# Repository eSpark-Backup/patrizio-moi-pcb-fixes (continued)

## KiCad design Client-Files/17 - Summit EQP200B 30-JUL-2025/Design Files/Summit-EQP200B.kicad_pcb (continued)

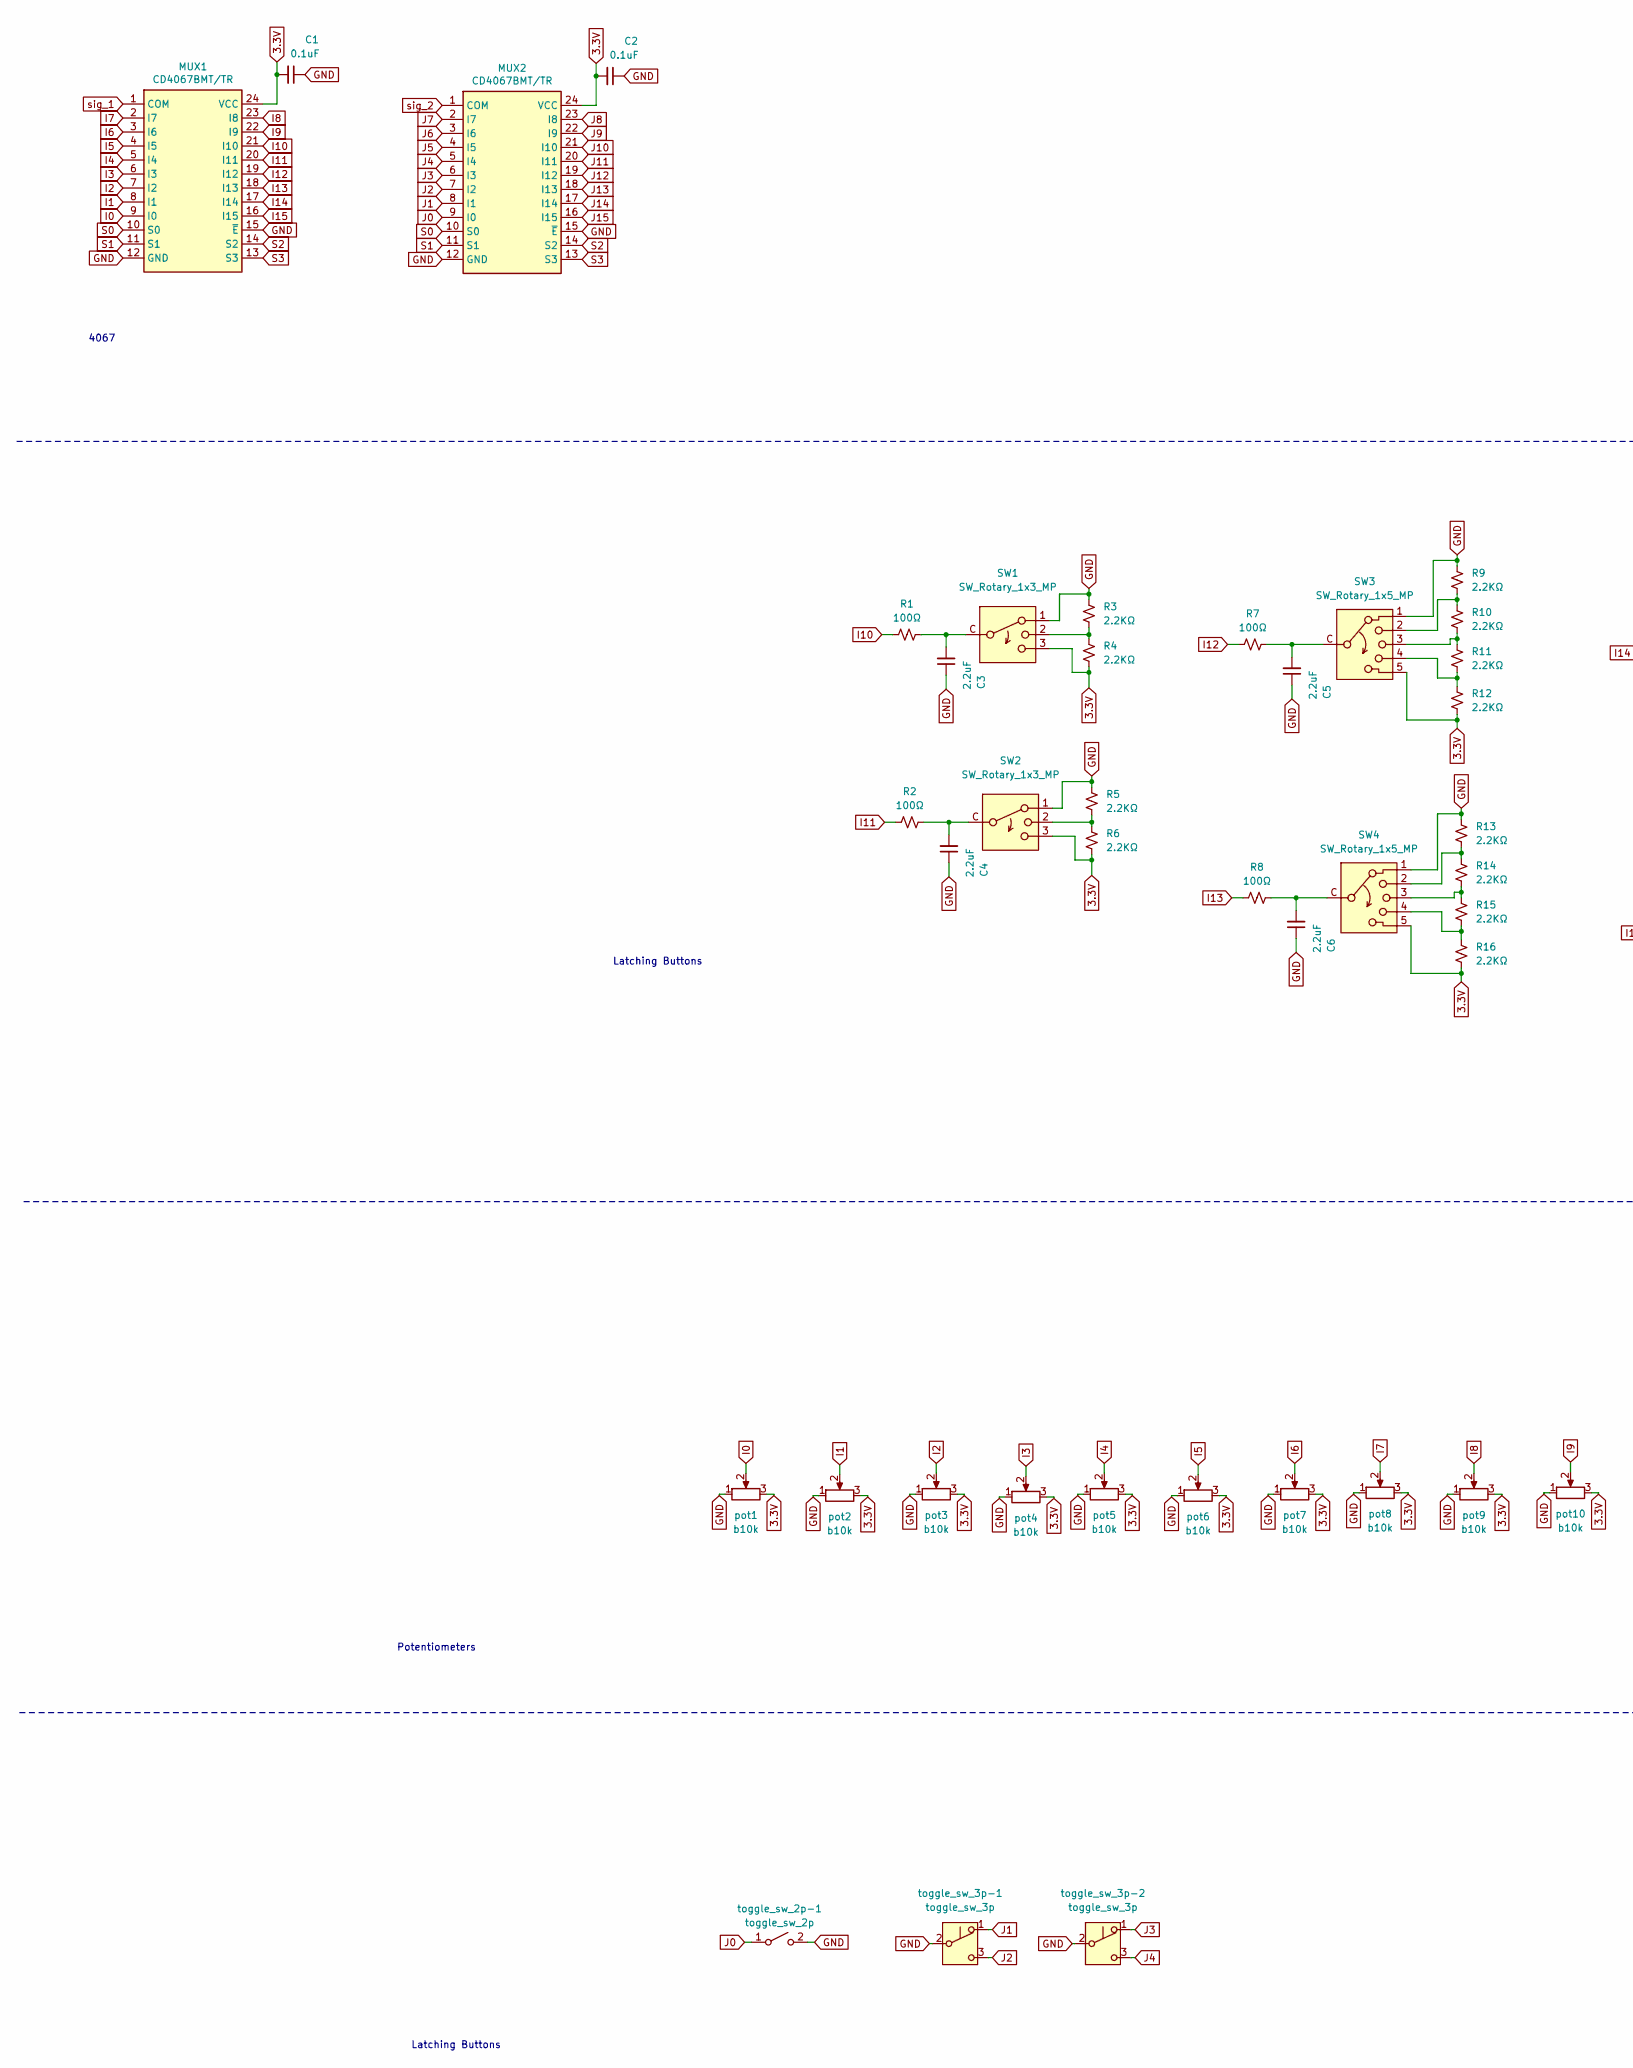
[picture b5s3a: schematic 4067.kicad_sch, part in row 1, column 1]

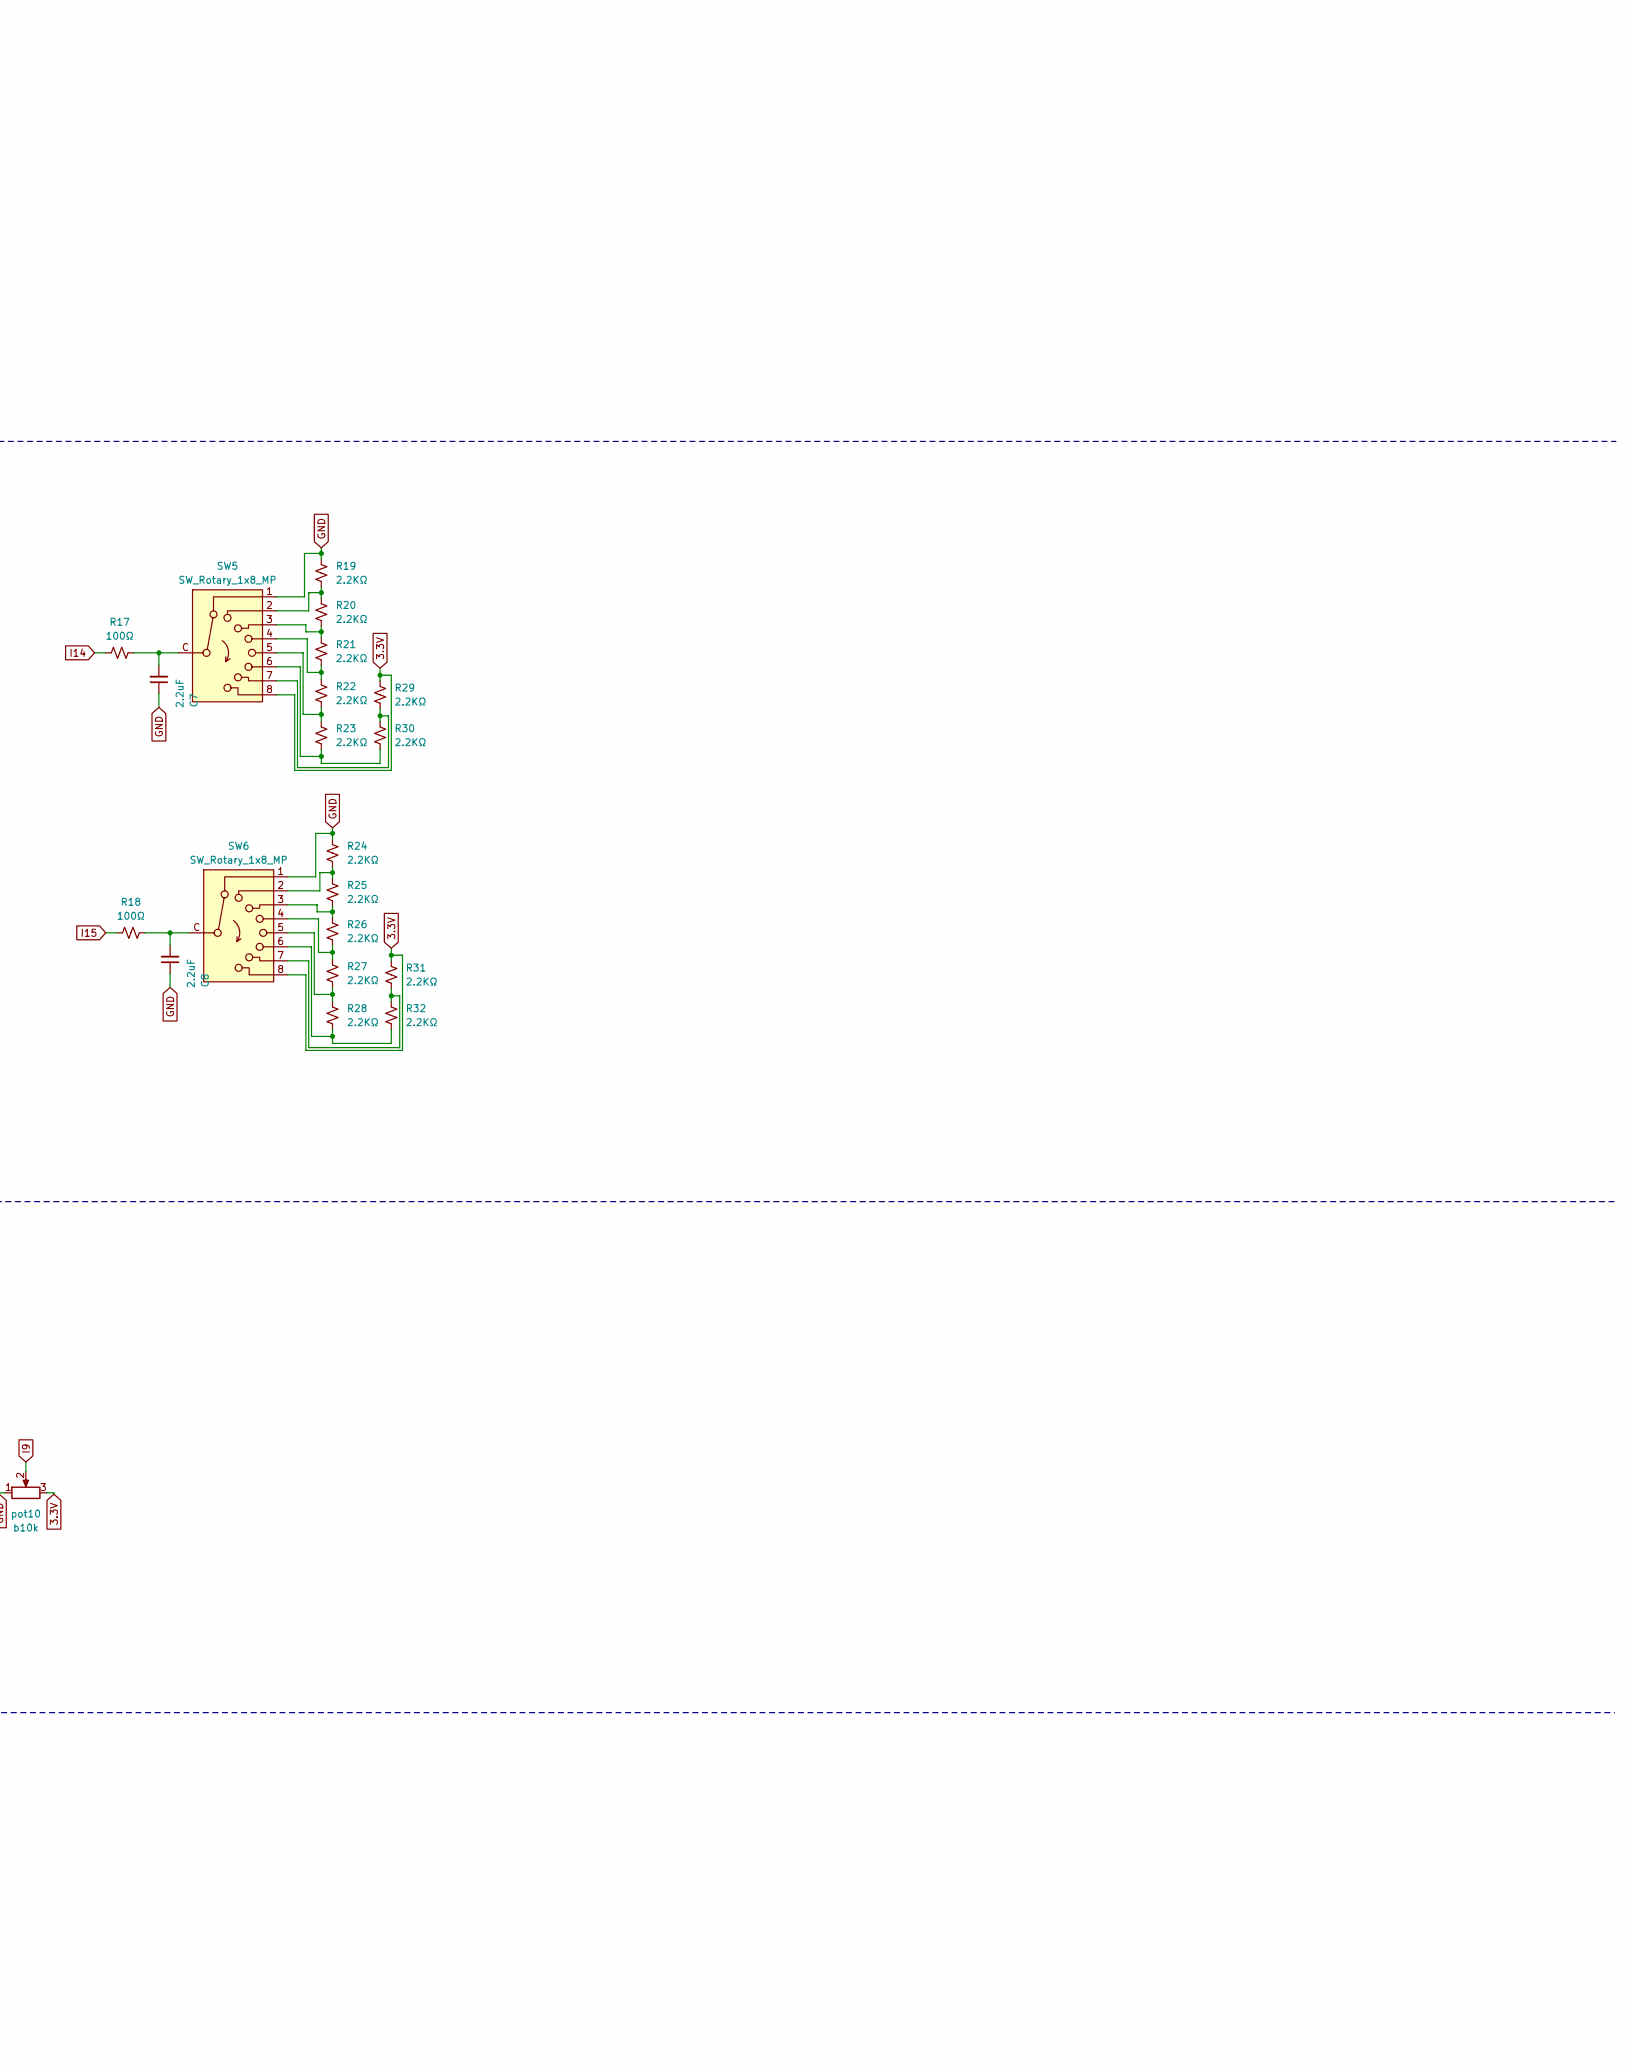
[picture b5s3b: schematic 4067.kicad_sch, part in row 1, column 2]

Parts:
C1, C2: 0.1uF; C_0402_1005Metric; LCSC Part Number C1525
C3, C4, C5, C6, C7, C8: 2.2uF; C_0402_1005Metric; LCSC Part Number C12530
MUX1, MUX2: CD4067BMT/TR; TSSOP-24_4.4x7.8mm_P0.65mm; LCSC Part Number C7432333
R1, R2, R7, R8, R17, R18: 100Ω; R_0402_1005Metric; LCSC Part Number C25076
R3, R4, R5, R6, R9, R10, R11, R12, R13, R14, R15, R16, R19, R20, R21, R22, R23, R24, R25, R26, R27, R28, R29, R30, R31, R32: 2.2KΩ; R_0402_1005Metric; LCSC Part Number C25879
SW1, SW2: SW_Rotary_1x3_MP; SW_Rotary_RS25-3P
SW3, SW4: SW_Rotary_1x5_MP; SW_Rotary_RS25-5P
SW5, SW6: SW_Rotary_1x8_MP; SW_Rotary_RS25-8P
pot1, pot2, pot3, pot4, pot5, pot6, pot7, pot8, pot9, pot10: b10k; Potentiometer_Alps_RK09K_Single_Vertical
toggle_sw_2p-1: toggle_sw_2p; Toggle_Switch-2-pins
toggle_sw_3p-1, toggle_sw_3p-2: toggle_sw_3p; Toggle_Switch-3-pins

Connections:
3.3V: C1.2, C2.2, MUX1.24 (VCC), MUX2.24 (VCC), R4.1, R6.1, R12.1, R16.1, R29.2, R31.2, SW1.3, SW2.3, SW3.5, SW4.5, SW5.8, SW6.8, pot1.3, pot2.3, pot3.3, pot4.3, pot5.3, pot6.3, pot7.3, pot8.3, pot9.3, pot10.3; also elsewhere on the board
GND: C1.1, C2.1, C3.1, C4.1, C5.1, C6.1, C7.1, C8.1, MUX1.12 (GND), MUX1.15 (~E), MUX2.12 (GND), MUX2.15 (~E), R3.2, R5.2, R9.2, R13.2, R19.2, R24.2, SW1.1, SW2.1, SW3.1, SW4.1, SW5.1, SW6.1, pot1.1, pot2.1, pot3.1, pot4.1, pot5.1, pot6.1, pot7.1, pot8.1, pot9.1, pot10.1, toggle_sw_2p-1.2 (B), toggle_sw_3p-1.2 (B), toggle_sw_3p-2.2 (B); also elsewhere on the board
I0: MUX1.9 (I0), pot1.2
I1: MUX1.8 (I1), pot2.2
I2: MUX1.7 (I2), pot3.2
I3: MUX1.6 (I3), pot4.2
I4: MUX1.5 (I4), pot5.2
I5: MUX1.4 (I5), pot6.2
I6: MUX1.3 (I6), pot7.2
I7: MUX1.2 (I7), pot8.2
I8: MUX1.23 (I8), pot9.2
I9: MUX1.22 (I9), pot10.2
I10: MUX1.21 (I10), R1.1
I11: MUX1.20 (I11), R2.1
I12: MUX1.19 (I12), R7.1
I13: MUX1.18 (I13), R8.1
I14: MUX1.17 (I14), R17.1
I15: MUX1.16 (I15), R18.1
J0: MUX2.9 (I0), toggle_sw_2p-1.1 (A)
J1: MUX2.8 (I1), toggle_sw_3p-1.1 (A)
J2: MUX2.7 (I2), toggle_sw_3p-1.3 (C)
J3: MUX2.6 (I3), toggle_sw_3p-2.1 (A)
J4: MUX2.5 (I4), toggle_sw_3p-2.3 (C)
J5: MUX2.4 (I5)
J6: MUX2.3 (I6)
J7: MUX2.2 (I7)
J8: MUX2.23 (I8)
J9: MUX2.22 (I9)
J10: MUX2.21 (I10)
J11: MUX2.20 (I11)
J12: MUX2.19 (I12)
J13: MUX2.18 (I13)
J14: MUX2.17 (I14)
J15: MUX2.16 (I15)
unnamed: C3.2, R1.2, SW1.C
unnamed: C4.2, R2.2, SW2.C
unnamed: C5.2, R7.2, SW3.C
unnamed: C6.2, R8.2, SW4.C
unnamed: C7.2, R17.2, SW5.C
unnamed: C8.2, R18.2, SW6.C
unnamed: R3.1, R4.2, SW1.2
unnamed: R5.1, R6.2, SW2.2
unnamed: R10.1, R11.2, SW3.3
unnamed: R9.1, R10.2, SW3.2
unnamed: R11.1, R12.2, SW3.4
unnamed: R13.1, R14.2, SW4.2
unnamed: R14.1, R15.2, SW4.3
unnamed: R15.1, R16.2, SW4.4
unnamed: R19.1, R20.2, SW5.2
unnamed: R20.1, R21.2, SW5.3
unnamed: R21.1, R22.2, SW5.4
unnamed: R22.1, R23.2, SW5.5
unnamed: R23.1, R30.1, SW5.6
unnamed: R24.1, R25.2, SW6.2
unnamed: R25.1, R26.2, SW6.3
unnamed: R26.1, R27.2, SW6.4
unnamed: R27.1, R28.2, SW6.5
unnamed: R28.1, R32.1, SW6.6
unnamed: R29.1, R30.2, SW5.7
unnamed: R31.1, R32.2, SW6.7
S0: MUX1.10 (S0), MUX2.10 (S0); also elsewhere on the board
S1: MUX1.11 (S1), MUX2.11 (S1); also elsewhere on the board
S2: MUX1.14 (S2), MUX2.14 (S2); also elsewhere on the board
S3: MUX1.13 (S3), MUX2.13 (S3); also elsewhere on the board
sig_1: MUX1.1 (COM); also elsewhere on the board
sig_2: MUX2.1 (COM); also elsewhere on the board

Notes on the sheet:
Latching Buttons
Potentiometers
4067

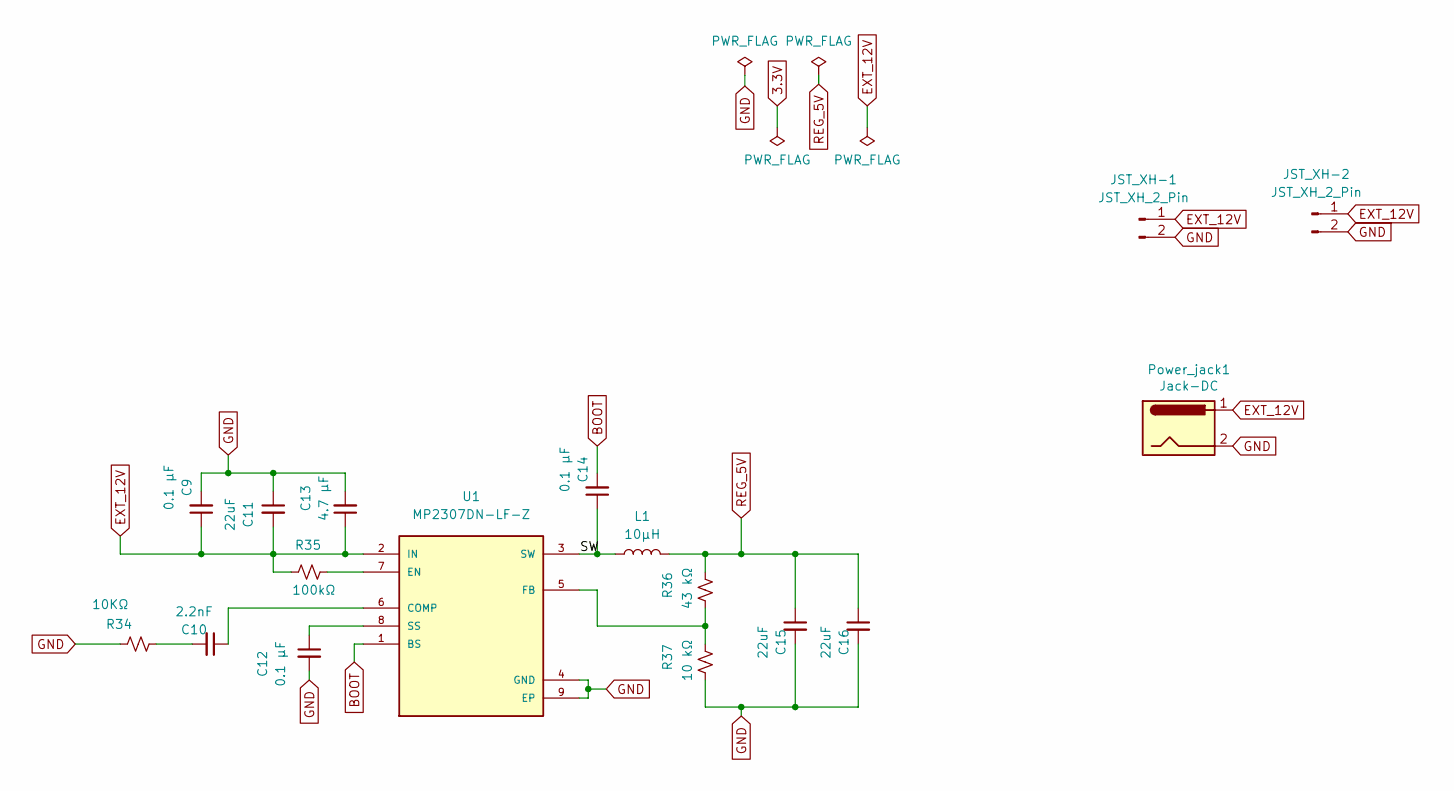
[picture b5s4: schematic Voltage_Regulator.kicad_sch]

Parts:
C9, C12, C14: 0.1 µF; C_0402_1005Metric; LCSC Part Number C1525
C10: 2.2nF; C_0603_1608Metric; LCSC Part Number C1604
C11, C15, C16: 22uF; C_0603_1608Metric; LCSC Part Number C59461
C13: 4.7 µF; C_0402_1005Metric; LCSC Part Number C23733
JST_XH-1, JST_XH-2: JST_XH_2_Pin; JST_XH_B2B-XH-A_1x02_P2.50mm_Vertical
L1: 10µH; L_Bourns-SRN8040_8x8.15mm; LCSC Part Number C37429
Power_jack1: Jack-DC; BarrelJack_Horizontal
R34: 10KΩ; R_0603_1608Metric; LCSC Part Number C25744
R35: 100kΩ; R_0603_1608Metric; LCSC Part Number C23212
R36: 43 kΩ; R_0402_1005Metric; LCSC Part Number C2906943
R37: 10 kΩ; R_0402_1005Metric; LCSC Part Number C25744
U1: MP2307DN-LF-Z; SOIC-8-1EP_3.9x4.9mm_P1.27mm_EP2.29x3mm_ThermalVias; PARTREV 1.9; LCSC Part Number C2928813

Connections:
/Voltage_Regulator/SW: C14.1, L1.1, U1.3 (SW)
BOOT: C14.2, U1.1 (BS)
EXT_12V: C9.1, C11.2, C13.1, JST_XH-1.1, JST_XH-2.1, Power_jack1.1, R35.1, U1.2 (IN)
GND: C9.2, C11.1, C12.2, C13.2, C15.2, C16.2, JST_XH-1.2, JST_XH-2.2, Power_jack1.2, R34.1, R37.2, U1.4 (GND), U1.9 (EP); also elsewhere on the board
unnamed: C10.2, R34.2
unnamed: C10.1, U1.6 (COMP)
unnamed: R35.2, U1.7 (EN)
unnamed: R36.2, R37.1, U1.5 (FB)
unnamed: C12.1, U1.8 (SS)
REG_5V: C15.1, C16.1, L1.2, R36.1; also elsewhere on the board

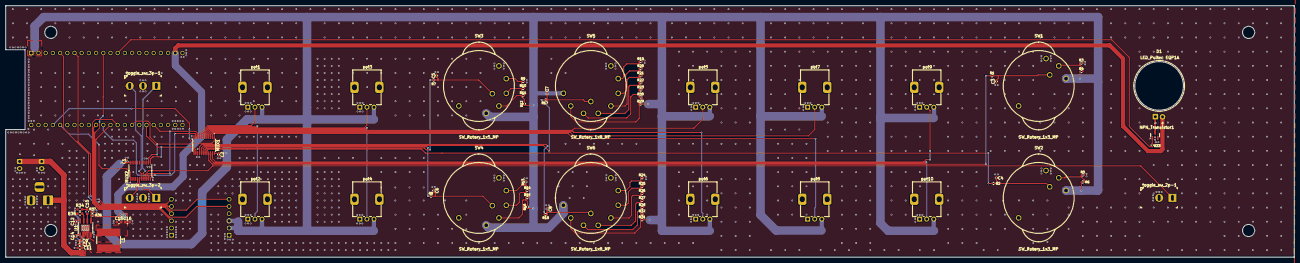
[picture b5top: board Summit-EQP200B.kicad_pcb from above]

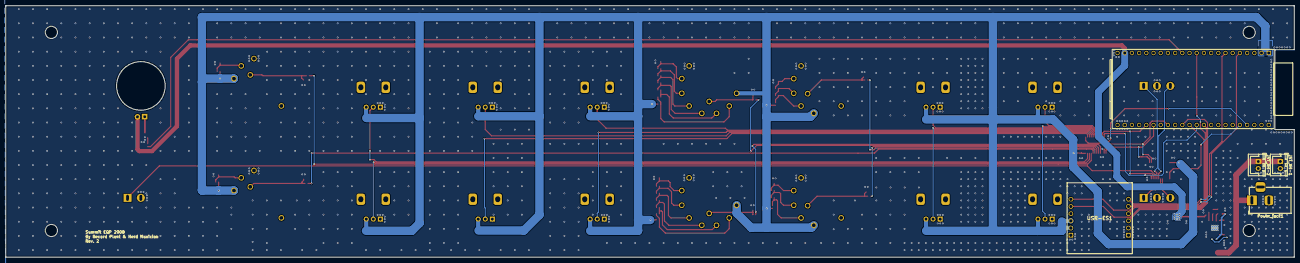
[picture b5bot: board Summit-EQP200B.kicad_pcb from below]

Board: 2 copper layers, 454.6 x 88.7 mm, 83 parts (5 on the bottom side), 73 nets.

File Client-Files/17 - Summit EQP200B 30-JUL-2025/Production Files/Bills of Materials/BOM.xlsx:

Comment | Designator | Footprint | LCSC Part Number | Quantity
CD4067BMT/TR | MUX1,MUX2 | Package_SO:TSSOP-24_4.4x7.8mm_P0.65mm | C7432333 | 2
MP2307DN-LF-Z | U1 | Package_SO:SOIC-8-1EP_3.9x4.9mm_P1.27mm_EP2.29x3mm_ThermalVias | C2928813 | 1
43â€¯kÎ© | R36 | Resistor_SMD:R_0402_1005Metric | C2906943 | 1
22uF | C11,C15,C16 | Capacitor_SMD:C_0603_1608Metric | C59461 | 3
10ÂµH | L1 | Inductor_SMD:L_Bourns-SRN8040_8x8.15mm | C37429 | 1
2.2KÎ© | R3,R4,R5,R6,R9,R10,R11,R12,R13,R14,R15,R16,R19,R20,R21,R22,R23,R24,R25,R26,R27,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 | Resistor_SMD:R_0402_1005Metric | C25879 | 26
10â€¯kÎ© | R37 | Resistor_SMD:R_0402_1005Metric | C25744 | 1
10KÎ© | R34 | Resistor_SMD:R_0603_1608Metric | C25744 | 1
100Î© | R1,R2,R7,R8,R17,R18 | Resistor_SMD:R_0402_1005Metric | C25076 | 6
4.7â€¯ÂµF | C13 | Capacitor_SMD:C_0402_1005Metric | C23733 | 1
100kÎ© | R35 | Resistor_SMD:R_0603_1608Metric | C23212 | 1
2.2uF | C3,C4,C5,C6,C7,C8 | Capacitor_SMD:C_0402_1005Metric | C12530 | 6
1kÎ© | R33 | Resistor_SMD:R_0402_1005Metric | C11702 | 1
2N2219 | NPN_Transistor1 | Package_TO_SOT_SMD:SOT-23 | C2150 | 1
2.2nF | C10 | Capacitor_SMD:C_0603_1608Metric | C1604 | 1
0.1â€¯ÂµF | C9,C12,C14 | Capacitor_SMD:C_0402_1005Metric | C1525 | 3
0.1uF | C1,C2 | Capacitor_SMD:C_0402_1005Metric | C1525 | 2
USR-ES1 | USR-ES1 | RF:USRES1 | NILL | 1
toggle_sw_3p | toggle_sw_3p-1,toggle_sw_3p-2 | digikey-footprints:Toggle_Switch-3-pins | NILL | 2
toggle_sw_2p | toggle_sw_2p-1 | digikey-footprints:Toggle_Switch-2-pins | NILL | 1
SW_Rotary_1x8_MP | SW5,SW6 | SW_Rotary:SW_Rotary_RS25-8P | NILL | 2
SW_Rotary_1x5_MP | SW3,SW4 | SW_Rotary:SW_Rotary_RS25-5P | NILL | 2
SW_Rotary_1x3_MP | SW1,SW2 | SW_Rotary:SW_Rotary_RS25-3P | NILL | 2
Jack-DC | Power_jack1 | Connector_BarrelJack:BarrelJack_Horizontal | NILL | 1
b10k | pot1,pot2,pot3,pot4,pot5,pot6,pot7,pot8,pot9,pot10 | Potentiometer_THT:Potentiometer_Alps_RK09K_Single_Vertical | NILL | 10
JST_XH_2_Pin | JST_XH-1,JST_XH-2 | Connector_JST:JST_XH_B2B-XH-A_1x02_P2.50mm_Vertical | NILL | 2
ESP32-S3-DevKitC | ESP32-S3-1 | Espressif:ESP32-S3-DEVKITC-1-N8R2-2 | NILL | 1
LED_Pultec EQP1A | D1 | LED_THT:LED_Pultech_1 | NILL | 1

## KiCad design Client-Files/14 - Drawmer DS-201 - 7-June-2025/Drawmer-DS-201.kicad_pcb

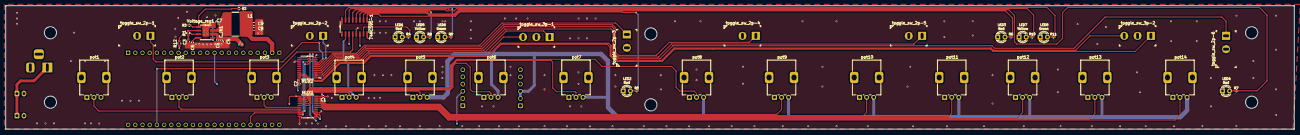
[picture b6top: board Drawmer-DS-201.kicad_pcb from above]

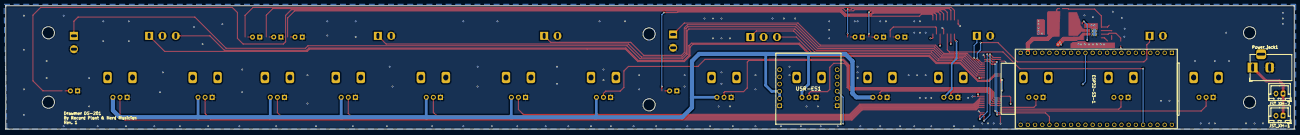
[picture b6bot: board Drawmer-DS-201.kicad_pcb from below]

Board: 4 copper layers, 454.4 x 43.5 mm, 62 parts (5 on the bottom side), 65 nets.

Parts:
74HC595-1: 74HC595; SOIC-16_3.9x9.9mm_P1.27mm
C1, C2: 0.1uF; C_0402_1005Metric
C3: 3.3 nF; C_0603_1608Metric
C4, C6, C7: 0.1 µF; C_0402_1005Metric
C5, C8, C9: 22uF; C_0603_1608Metric
C_IN1: 4.7 µF; C_0402_1005Metric
ESP32-S3-1: ESP32-S3-DevKitC; ESP32-S3-DEVKITC-1-N8R2-2
JST_XH-1, JST_XH-2: JST_XH_2_Pin; JST_XH_B2B-XH-A_1x02_P2.50mm_Vertical
L1: 10µH; L_Bourns-SRN8040_8x8.15mm
LED1, LED2, LED3, LED4: Red; LED_D3.0mm_Clear-2
LED5, LED7: Yellow; LED_D3.0mm_Clear-2
LED6, LED8: Green; LED_D3.0mm_Clear-2
MUX1, MUX2: CD4067BMT/TR; TSSOP-24_4.4x7.8mm_P0.65mm
Power_jack1: Jack-DC; BarrelJack_Horizontal
R1: 6.8kΩ; R_0603_1608Metric
R2: 43 kΩ; R_0402_1005Metric
R3: 10 kΩ; R_0402_1005Metric
R4, R5, R6, R7, R8, R9, R10, R11: 330Ω; R_0402_1005Metric
R12: 100kΩ; R_0603_1608Metric
USR-ES1: USR-ES1; USRES1
Voltage_reg1: MP2307DN-LF-Z; SOIC-8-1EP_3.9x4.9mm_P1.27mm_EP2.29x3mm_ThermalVias
pot1, pot2, pot3, pot4, pot5, pot6, pot7, pot8, pot9, pot10, pot11, pot12, pot13, pot14: b10k; Potentiometer_Alps_RK09K_Single_Vertical
toggle_sw_2p-1, toggle_sw_2p-2, toggle_sw_2p-3, toggle_sw_2p-4, toggle_sw_2p-5, toggle_sw_2p-6: toggle_sw_2p; Toggle_Switch-2-pins
toggle_sw_3p-1, toggle_sw_3p-2: toggle_sw_3p; Toggle_Switch-3-pins

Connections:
3.3V: 74HC595-1.10 (~SRCLR), 74HC595-1.16 (VCC), C1.2, C2.2, ESP32-S3-1.1 (3V3), ESP32-S3-1.2 (3V3), MUX1.24 (VCC), MUX2.24 (VCC), USR-ES1.B2 (3V3_1), USR-ES1.B3 (3V3_2), pot1.3, pot2.3, pot3.3, pot4.3, pot5.3, pot6.3, pot7.3, pot8.3, pot9.3, pot10.3, pot11.3, pot12.3, pot13.3, pot14.3
/LEDs/LED_A_QA: 74HC595-1.15 (QA), R4.2
/LEDs/LED_A_QB: 74HC595-1.1 (QB), R5.2
/LEDs/LED_A_QC: 74HC595-1.2 (QC), R6.2
/LEDs/LED_A_QD: 74HC595-1.3 (QD), R7.2
/LEDs/LED_A_QE: 74HC595-1.4 (QE), R8.2
/LEDs/LED_A_QF: 74HC595-1.5 (QF), R10.2
/LEDs/LED_A_QG: 74HC595-1.6 (QG), R9.2
/LEDs/LED_A_QH: 74HC595-1.7 (QH), R11.2
BOOT: C7.2, Voltage_reg1.1 (BS)
CS: ESP32-S3-1.5 (GPIO5/ADC1_CH4), USR-ES1.A5 (CS)
EXT_12V: C4.1, C5.2, C_IN1.1, JST_XH-1.1, JST_XH-2.1, Power_jack1.1, R12.1, Voltage_reg1.2 (IN)
GND: 74HC595-1.8 (GND), 74HC595-1.13 (~OE), C1.1, C2.1, C3.2, C4.2, C5.1, C6.2, C8.2, C9.2, C_IN1.2, ESP32-S3-1.22 (GND), ESP32-S3-1.23 (GND), ESP32-S3-1.24 (GND), ESP32-S3-1.44 (GND), JST_XH-1.2, JST_XH-2.2, LED1.1 (K), LED2.1 (K), LED3.1 (K), LED4.1 (K), LED5.1 (K), LED6.1 (K), LED7.1 (K), LED8.1 (K), MUX1.12 (GND), MUX1.15 (~E), MUX2.12 (GND), MUX2.15 (~E), Power_jack1.2, R3.2, USR-ES1.A1 (GND_1), USR-ES1.A2 (GND_2), USR-ES1.B1 (GND_3), Voltage_reg1.4 (GND), Voltage_reg1.9 (EP), pot1.1, pot2.1, pot3.1, pot4.1, pot5.1, pot6.1, pot7.1, pot8.1, pot9.1, pot10.1, pot11.1, pot12.1, pot13.1, pot14.1, toggle_sw_2p-1.2 (B), toggle_sw_2p-2.2 (B), toggle_sw_2p-3.2 (B), toggle_sw_2p-4.2 (B), toggle_sw_2p-5.2 (B), toggle_sw_2p-6.2 (B), toggle_sw_3p-1.2 (B), toggle_sw_3p-2.2 (B)
I0: MUX1.9 (I0), pot1.2
I1: MUX1.8 (I1), pot2.2
I2: MUX1.7 (I2), pot3.2
I3: MUX1.6 (I3), pot4.2
I4: MUX1.5 (I4), pot5.2
I5: MUX1.4 (I5), pot6.2
I6: MUX1.3 (I6), pot7.2
I7: MUX1.2 (I7), pot8.2
I8: MUX1.23 (I8), pot9.2
I9: MUX1.22 (I9), pot10.2
I10: MUX1.21 (I10), pot11.2
I11: MUX1.20 (I11), pot12.2
I12: MUX1.19 (I12), pot13.2
I13: MUX1.18 (I13), pot14.2
INT: ESP32-S3-1.7 (GPIO7/ADC1_CH6), USR-ES1.A6 (INT)
J0: MUX2.9 (I0), toggle_sw_2p-1.1 (A)
J1: MUX2.8 (I1), toggle_sw_2p-2.1 (A)
J2: MUX2.7 (I2), toggle_sw_2p-3.1 (A)
J3: MUX2.6 (I3), toggle_sw_2p-4.1 (A)
J4: MUX2.5 (I4), toggle_sw_2p-5.1 (A)
J5: MUX2.4 (I5), toggle_sw_2p-6.1 (A)
J6: MUX2.3 (I6), toggle_sw_3p-1.1 (A)
J7: MUX2.2 (I7), toggle_sw_3p-1.3 (C)
J8: MUX2.23 (I8), toggle_sw_3p-2.1 (A)
J9: MUX2.22 (I9), toggle_sw_3p-2.3 (C)
MISO: ESP32-S3-1.33 (GPIO36), USR-ES1.B6 (MISO)
MOSI: ESP32-S3-1.32 (GPIO35), USR-ES1.A3 (MOSI)
unnamed: C3.1, R1.1
unnamed: LED1.2 (A), R4.1
unnamed: LED2.2 (A), R5.1
unnamed: LED3.2 (A), R6.1
unnamed: LED4.2 (A), R7.1
unnamed: LED5.2 (A), R8.1
unnamed: LED6.2 (A), R9.1
unnamed: LED7.2 (A), R10.1
unnamed: LED8.2 (A), R11.1
unnamed: R1.2, Voltage_reg1.6 (COMP)
unnamed: R12.2, Voltage_reg1.7 (EN)
unnamed: R2.2, R3.1, Voltage_reg1.5 (FB)
unnamed: C6.1, Voltage_reg1.8 (SS)
unnamed: C7.1, L1.1, Voltage_reg1.3 (SW)
RCLK_latch: 74HC595-1.12 (RCLK), ESP32-S3-1.40 (GPIO2/ADC1_CH1)
REG_5V: C8.1, C9.1, ESP32-S3-1.21 (5V), L1.2, R2.1
RST: ESP32-S3-1.35 (GPIO38), USR-ES1.B5 (RST)
S0: ESP32-S3-1.27 (GPIO21), MUX1.10 (S0), MUX2.10 (S0)
S1: ESP32-S3-1.34 (GPIO37), MUX1.11 (S1), MUX2.11 (S1)
S2: ESP32-S3-1.30 (GPIO45), MUX1.14 (S2), MUX2.14 (S2)
S3: ESP32-S3-1.28 (GPIO47), MUX1.13 (S3), MUX2.13 (S3)
SCLK: 74HC595-1.11 (SRCLK), ESP32-S3-1.11 (GPIO18/ADC2_CH7), USR-ES1.A4 (SCLK)
SER: 74HC595-1.14 (SER), ESP32-S3-1.4 (GPIO4/ADC1_CH3)
sig_1: ESP32-S3-1.41 (GPIO1/ADC1_CH0), MUX1.1 (COM)
sig_2: ESP32-S3-1.13 (GPIO3/ADC1_CH2), MUX2.1 (COM)

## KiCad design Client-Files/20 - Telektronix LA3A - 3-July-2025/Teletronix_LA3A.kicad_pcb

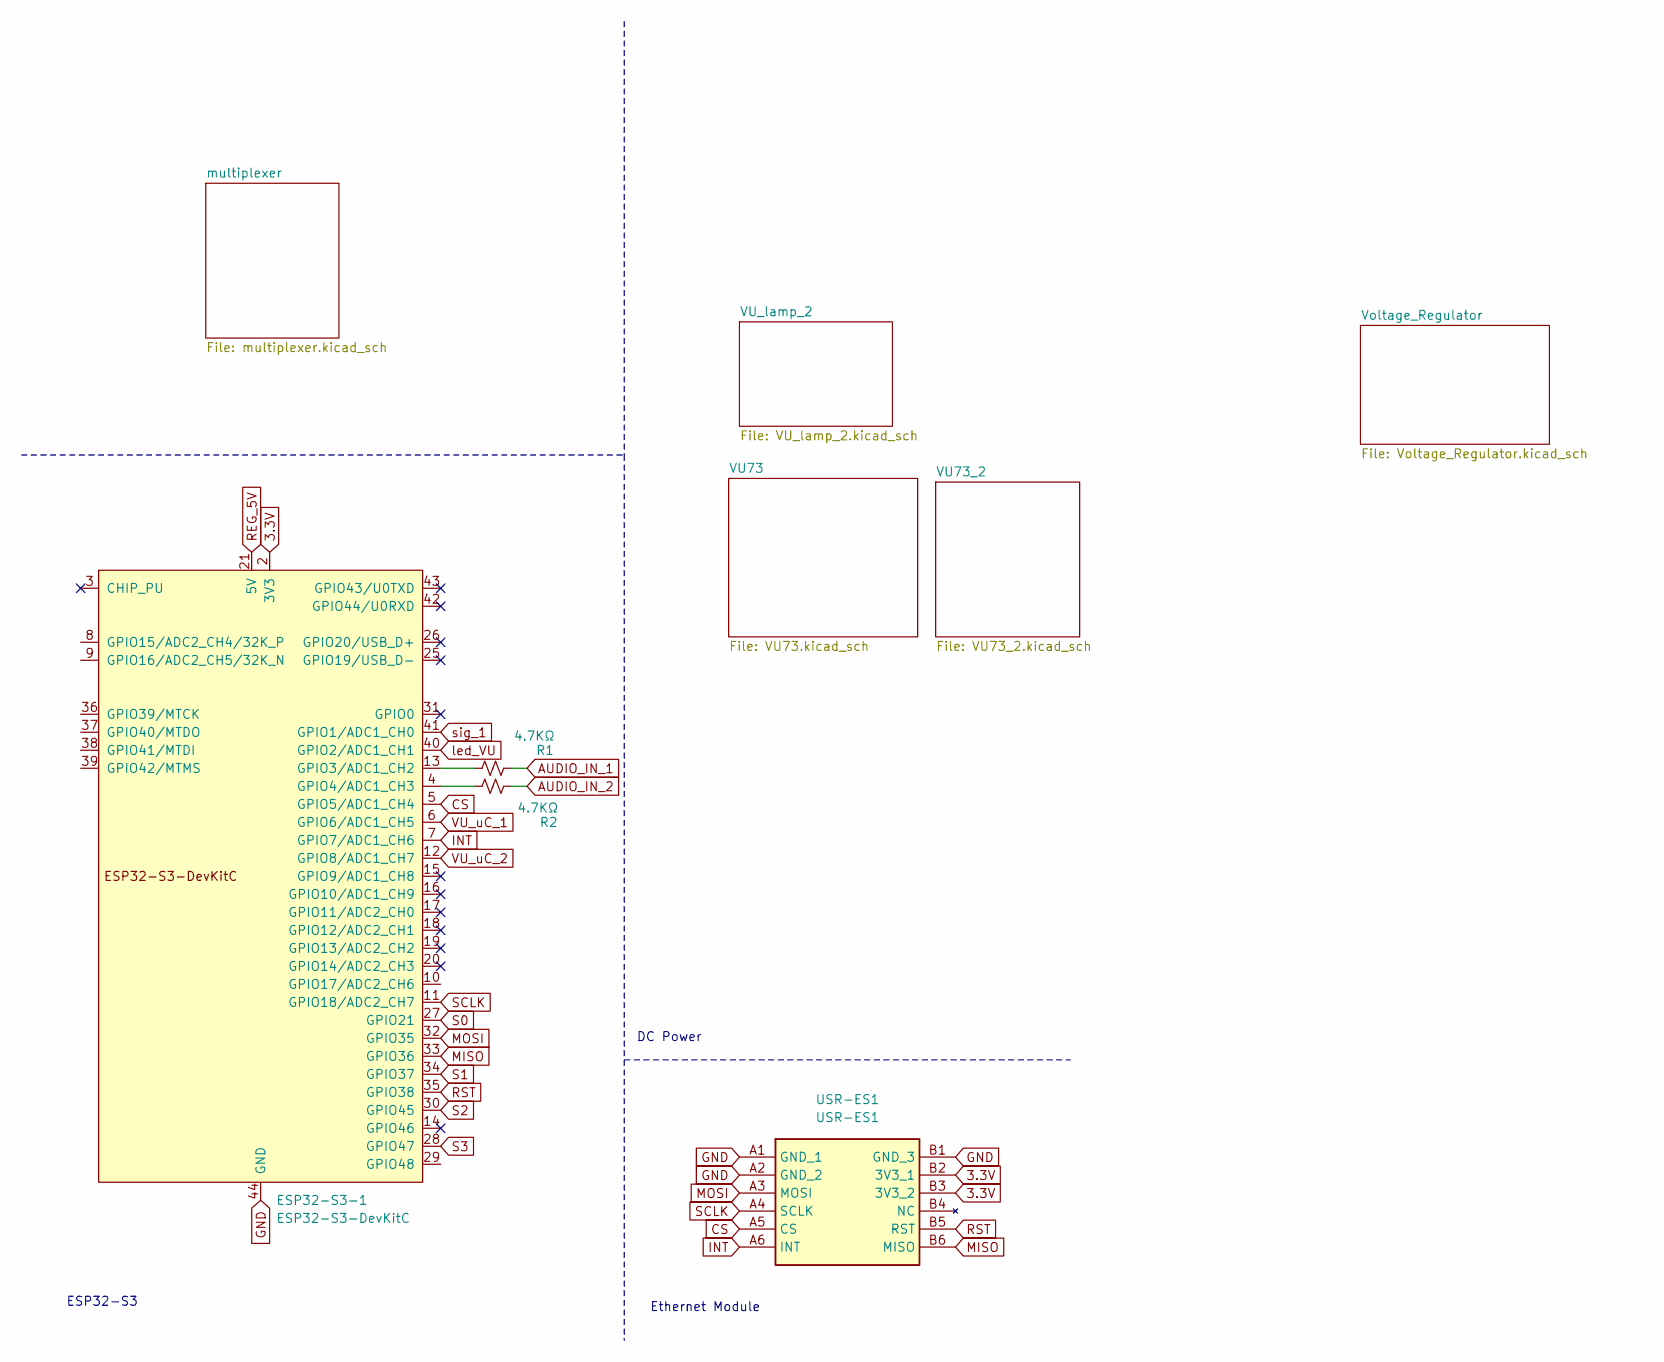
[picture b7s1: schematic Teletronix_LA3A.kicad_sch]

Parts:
ESP32-S3-1: ESP32-S3-DevKitC; ESP32-S3-DEVKITC-1-N8R2-2
R1, R2: 4.7KΩ; R_0402_1005Metric; LCSC Part Number C25900
USR-ES1: USR-ES1; USRES1; Manufacturer_Part_Number USR-ES1

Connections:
3.3V: ESP32-S3-1.1 (3V3), ESP32-S3-1.2 (3V3), USR-ES1.B2 (3V3_1), USR-ES1.B3 (3V3_2); also elsewhere on the board
AUDIO_IN_1: R1.1; also elsewhere on the board
AUDIO_IN_2: R2.1; also elsewhere on the board
CS: ESP32-S3-1.5 (GPIO5/ADC1_CH4), USR-ES1.A5 (CS)
GND: ESP32-S3-1.22 (GND), ESP32-S3-1.23 (GND), ESP32-S3-1.24 (GND), ESP32-S3-1.44 (GND), USR-ES1.A1 (GND_1), USR-ES1.A2 (GND_2), USR-ES1.B1 (GND_3); also elsewhere on the board
INT: ESP32-S3-1.7 (GPIO7/ADC1_CH6), USR-ES1.A6 (INT)
MISO: ESP32-S3-1.33 (GPIO36), USR-ES1.B6 (MISO)
MOSI: ESP32-S3-1.32 (GPIO35), USR-ES1.A3 (MOSI)
unnamed: ESP32-S3-1.13 (GPIO3/ADC1_CH2), R1.2
unnamed: ESP32-S3-1.4 (GPIO4/ADC1_CH3), R2.2
REG_5V: ESP32-S3-1.21 (5V); also elsewhere on the board
RST: ESP32-S3-1.35 (GPIO38), USR-ES1.B5 (RST)
S0: ESP32-S3-1.27 (GPIO21); also elsewhere on the board
S1: ESP32-S3-1.34 (GPIO37); also elsewhere on the board
S2: ESP32-S3-1.30 (GPIO45); also elsewhere on the board
S3: ESP32-S3-1.28 (GPIO47); also elsewhere on the board
SCLK: ESP32-S3-1.11 (GPIO18/ADC2_CH7), USR-ES1.A4 (SCLK)
VU_uC_1: ESP32-S3-1.6 (GPIO6/ADC1_CH5); also elsewhere on the board
VU_uC_2: ESP32-S3-1.12 (GPIO8/ADC1_CH7); also elsewhere on the board
led_VU: ESP32-S3-1.40 (GPIO2/ADC1_CH1); also elsewhere on the board
sig_1: ESP32-S3-1.41 (GPIO1/ADC1_CH0); also elsewhere on the board

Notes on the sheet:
Ethernet Module
DC Power
ESP32-S3

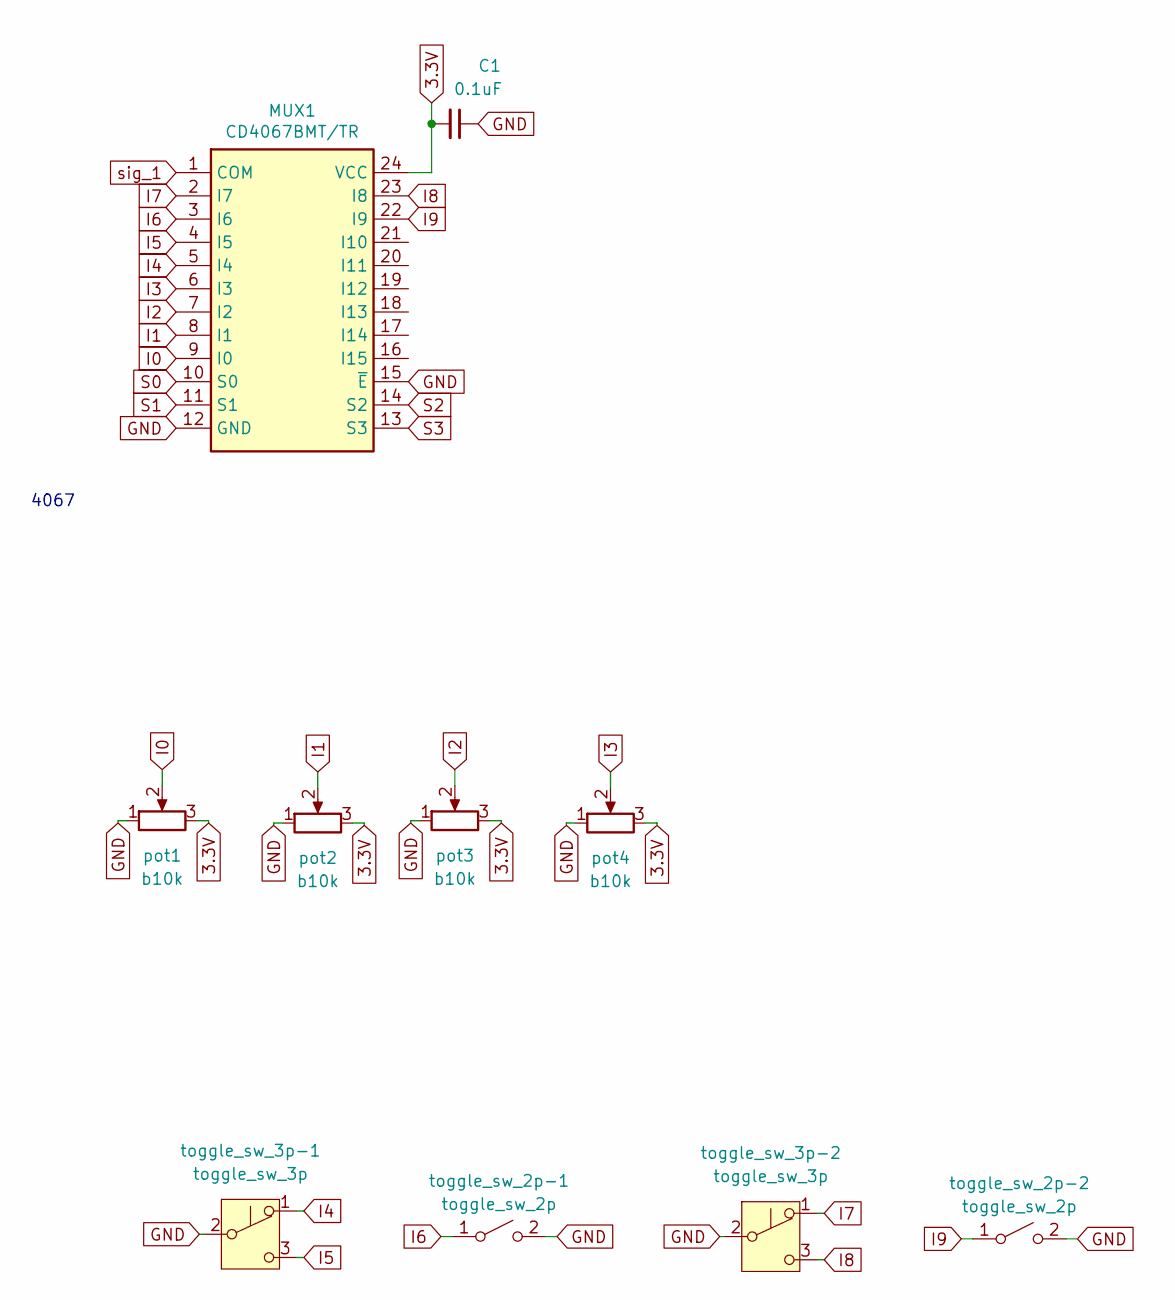
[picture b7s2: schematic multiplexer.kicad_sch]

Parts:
C1: 0.1uF; C_0402_1005Metric; LCSC Part Number C1525
MUX1: CD4067BMT/TR; TSSOP-24_4.4x7.8mm_P0.65mm; LCSC Part Number C7432333
pot1, pot2, pot3, pot4: b10k; Potentiometer_Alps_RK09K_Single_Vertical
toggle_sw_2p-1, toggle_sw_2p-2: toggle_sw_2p; Toggle_Switch-2-pins
toggle_sw_3p-1, toggle_sw_3p-2: toggle_sw_3p; Toggle_Switch-3-pins

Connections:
3.3V: C1.2, MUX1.24 (VCC), pot1.3, pot2.3, pot3.3, pot4.3; also elsewhere on the board
GND: C1.1, MUX1.12 (GND), MUX1.15 (~E), pot1.1, pot2.1, pot3.1, pot4.1, toggle_sw_2p-1.2 (B), toggle_sw_2p-2.2 (B), toggle_sw_3p-1.2 (B), toggle_sw_3p-2.2 (B); also elsewhere on the board
I0: MUX1.9 (I0), pot1.2
I1: MUX1.8 (I1), pot2.2
I2: MUX1.7 (I2), pot3.2
I3: MUX1.6 (I3), pot4.2
I4: MUX1.5 (I4), toggle_sw_3p-1.1 (A)
I5: MUX1.4 (I5), toggle_sw_3p-1.3 (C)
I6: MUX1.3 (I6), toggle_sw_2p-1.1 (A)
I7: MUX1.2 (I7), toggle_sw_3p-2.1 (A)
I8: MUX1.23 (I8), toggle_sw_3p-2.3 (C)
I9: MUX1.22 (I9), toggle_sw_2p-2.1 (A)
S0: MUX1.10 (S0); also elsewhere on the board
S1: MUX1.11 (S1); also elsewhere on the board
S2: MUX1.14 (S2); also elsewhere on the board
S3: MUX1.13 (S3); also elsewhere on the board
sig_1: MUX1.1 (COM); also elsewhere on the board

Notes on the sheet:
4067
